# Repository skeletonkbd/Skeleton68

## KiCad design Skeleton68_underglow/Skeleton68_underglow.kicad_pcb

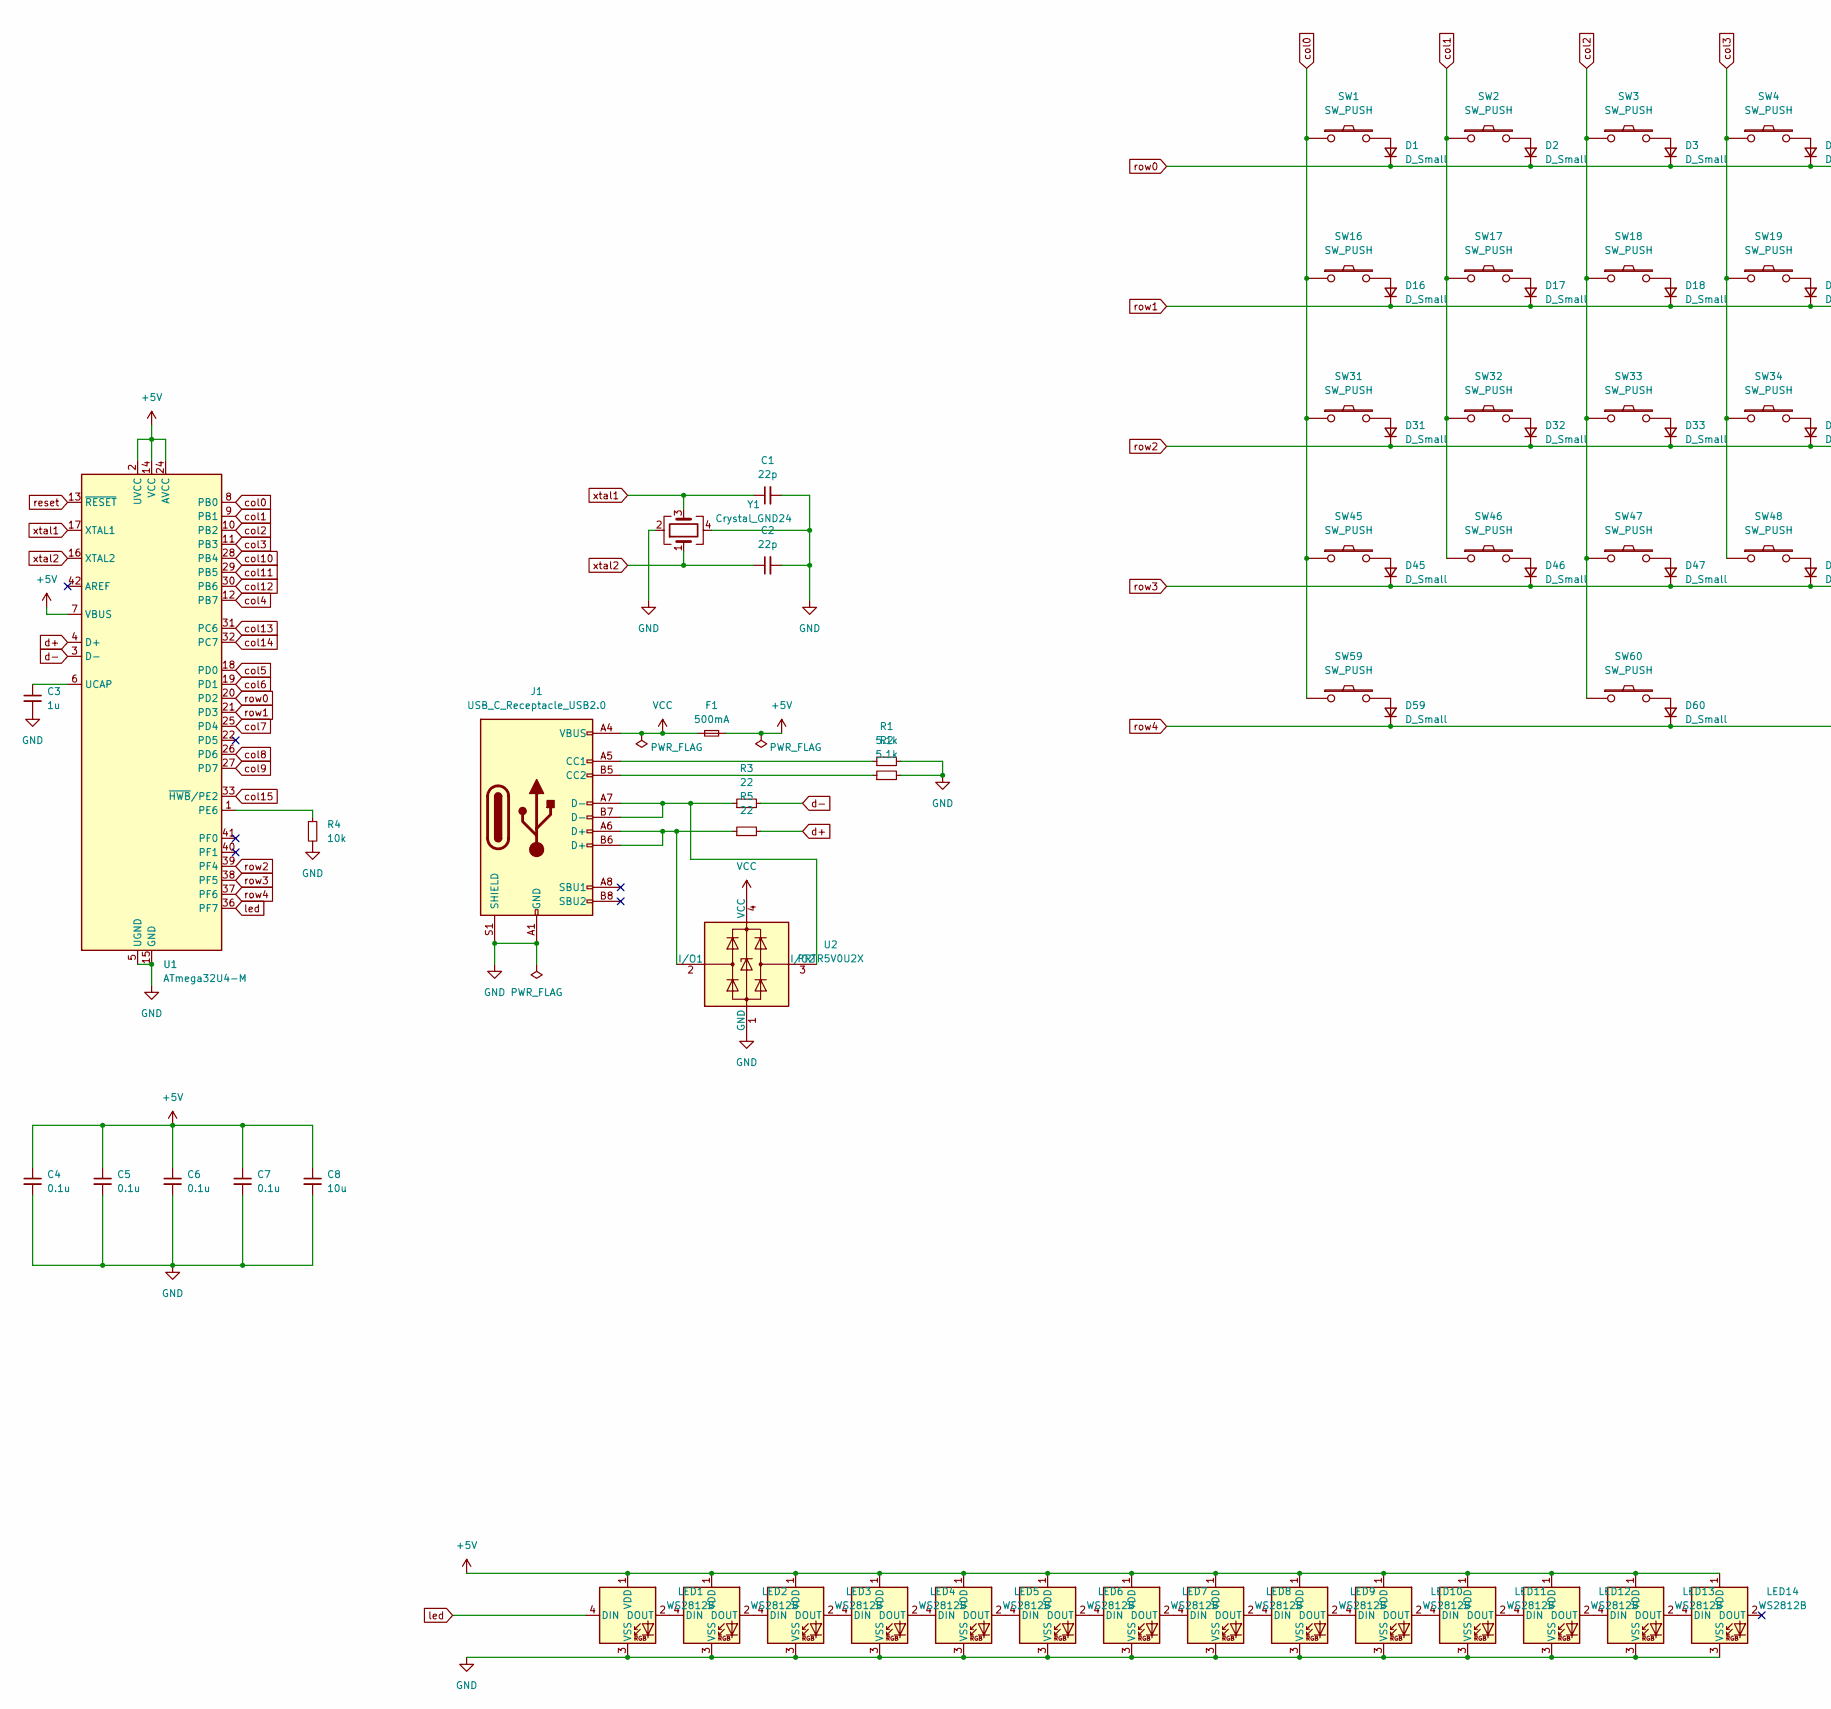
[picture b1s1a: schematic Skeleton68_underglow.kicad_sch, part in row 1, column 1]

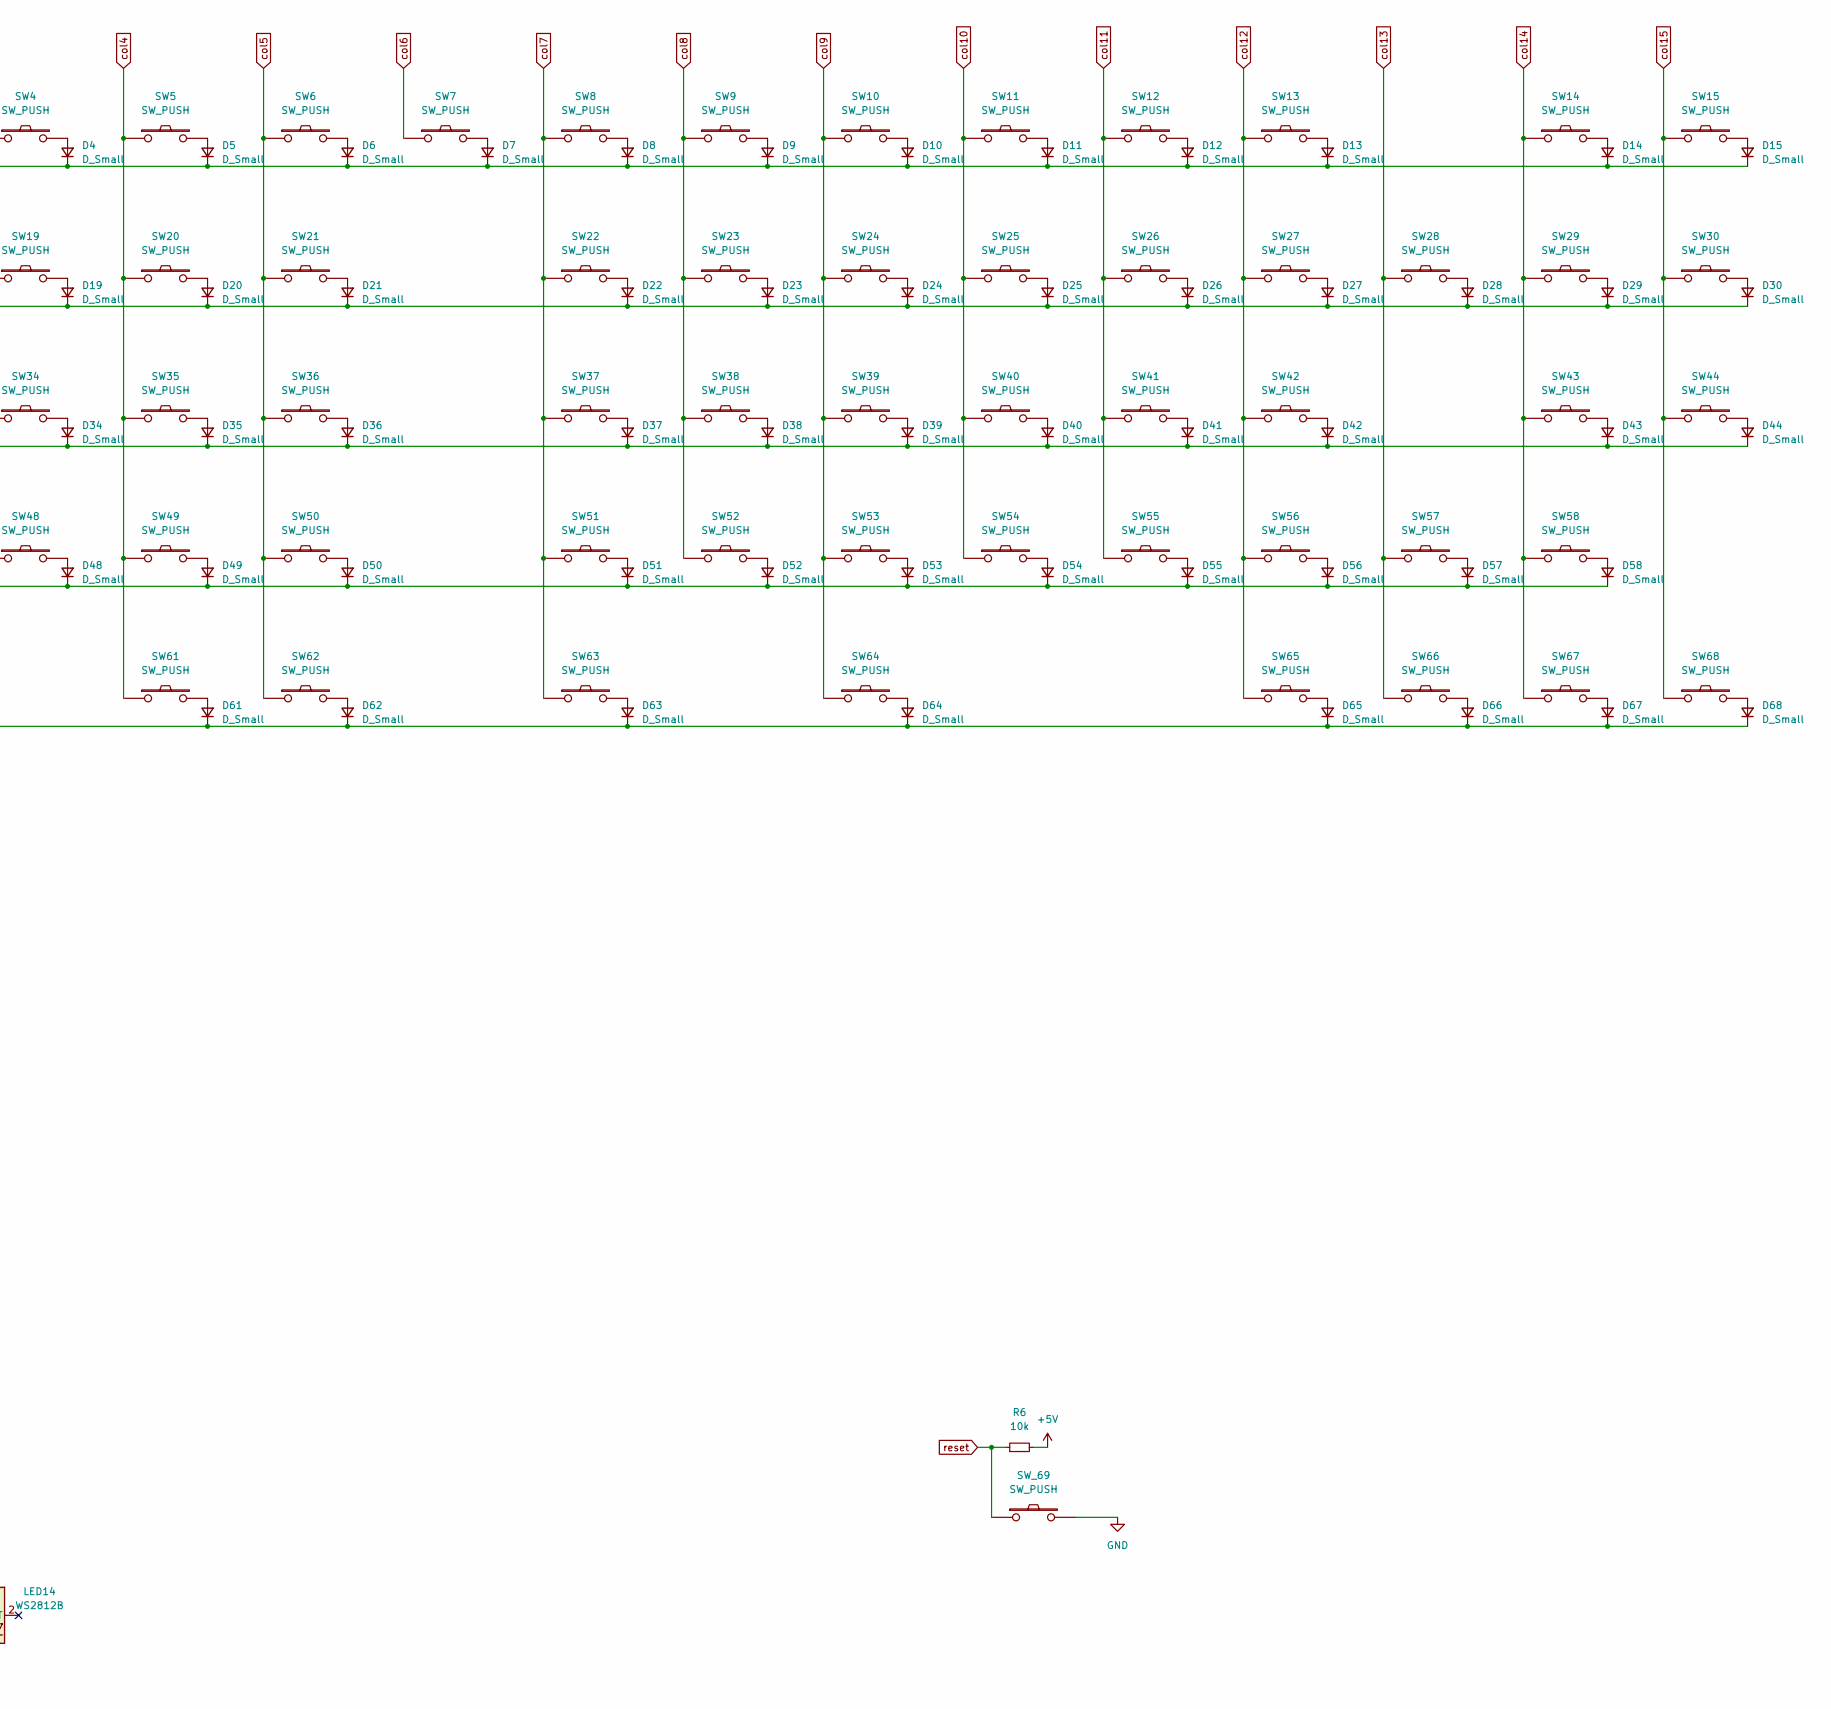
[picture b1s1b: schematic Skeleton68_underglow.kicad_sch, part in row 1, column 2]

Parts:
C1, C2: 22p; C_0805_2012Metric; LCSC C1804
C3: 1u; C_0805_2012Metric; LCSC C28323
C4, C5, C6, C7: 0.1u; C_0805_2012Metric; LCSC C49678
C8: 10u; C_0805_2012Metric; LCSC C15850
D1, D2, D3, D4, D5, D6, D7, D8, D9, D10, D11, D12, D13, D14, D15, D16, D17, D18, D19, D20, D21, D22, D23, D24, D25, D26, D27, D28, D29, D30, D31, D32, D33, D34, D35, D36, D37, D38, D39, D40, D41, D42, D43, D44, D45, D46, D47, D48, D49, D50, D51, D52, D53, D54, D55, D56, D57, D58, D59, D60, D61, D62, D63, D64, D65, D66, D67, D68: D_Small; D_SOD-123; LCSC C81598
F1: 500mA; Fuse_1206_3216Metric; LCSC C70069
J1: USB_C_Receptacle_USB2.0; USB_C_Receptacle_Palconn_UTC16-G; LCSC C167321
LED1, LED2, LED3, LED4, LED5, LED6, LED7, LED8, LED9, LED10, LED11, LED12, LED13, LED14: WS2812B; LED_WS2812B_PLCC4_5.0x5.0mm_P3.2mm; LCSC C2874885
R1, R2: 5.1k; R_0805_2012Metric; LCSC C27834
R3, R5: 22; R_0805_2012Metric; LCSC C17561
R4, R6: 10k; R_0805_2012Metric; LCSC C17414
SW1, SW2, SW3, SW4, SW5, SW6, SW7, SW8, SW9, SW10, SW11, SW12, SW13, SW15, SW17, SW18, SW19, SW20, SW21, SW22, SW23, SW24, SW25, SW26, SW27, SW28, SW30, SW32, SW33, SW34, SW35, SW36, SW37, SW38, SW39, SW40, SW41, SW42, SW44, SW46, SW47, SW48, SW49, SW50, SW51, SW52, SW53, SW54, SW55, SW56, SW58, SW62, SW66, SW67, SW68: SW_PUSH; MXOnly-1U-Hotswap; LCSC C2803348
SW14: SW_PUSH; MXOnly-2U-Hotswap; LCSC C2803348
SW16, SW29, SW59, SW60, SW64, SW65: SW_PUSH; MXOnly-1.5U-Hotswap; LCSC C2803348
SW31, SW57: SW_PUSH; MXOnly-1.75U-Hotswap; LCSC C2803348
SW43, SW45: SW_PUSH; MXOnly-2.25U-Hotswap; LCSC C2803348
SW61: SW_PUSH; MXOnly-2U-Hotswap-ReversedStabilizers; LCSC C2803348
SW63: SW_PUSH; MXOnly-2.75U-Hotswap-ReversedStabilizers; LCSC C2803348
SW_69: SW_PUSH; SW_SPST_SKQG_WithStem; LCSC C455263
U1: ATmega32U4-M; QFN-44-1EP_7x7mm_P0.5mm_EP5.2x5.2mm; LCSC C45874
U2: PRTR5V0U2X; SOT-143; LCSC C2827688
Y1: Crystal_GND24; Crystal_SMD_3225-4Pin_3.2x2.5mm; LCSC C13738

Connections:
+5V: C4.1, C5.1, C6.1, C7.1, C8.1, F1.2, LED1.1 (VDD), LED2.1 (VDD), LED3.1 (VDD), LED4.1 (VDD), LED5.1 (VDD), LED6.1 (VDD), LED7.1 (VDD), LED8.1 (VDD), LED9.1 (VDD), LED10.1 (VDD), LED11.1 (VDD), LED12.1 (VDD), LED13.1 (VDD), LED14.1 (VDD), R6.2, U1.2 (UVCC), U1.7 (VBUS), U1.14 (VCC), U1.24 (AVCC), U1.34 (VCC), U1.44 (AVCC)
GND: C1.2, C2.2, C3.2, C4.2, C5.2, C6.2, C7.2, C8.2, J1.A1 (GND), J1.A12 (GND), J1.B1 (GND), J1.B12 (GND), J1.S1 (SHIELD), LED1.3 (VSS), LED2.3 (VSS), LED3.3 (VSS), LED4.3 (VSS), LED5.3 (VSS), LED6.3 (VSS), LED7.3 (VSS), LED8.3 (VSS), LED9.3 (VSS), LED10.3 (VSS), LED11.3 (VSS), LED12.3 (VSS), LED13.3 (VSS), LED14.3 (VSS), R1.2, R2.2, R4.2, SW_69.2, U1.5 (UGND), U1.15 (GND), U1.23 (GND), U1.35 (GND), U1.43 (GND), U1.45 (GND), U2.1 (GND), Y1.2, Y1.4
unnamed: C3.1, U1.6 (UCAP)
unnamed: D1.2 (A), SW1.2
unnamed: D2.2 (A), SW2.2
unnamed: D3.2 (A), SW3.2
unnamed: D4.2 (A), SW4.2
unnamed: D5.2 (A), SW5.2
unnamed: D6.2 (A), SW6.2
unnamed: D7.2 (A), SW7.2
unnamed: D8.2 (A), SW8.2
unnamed: D9.2 (A), SW9.2
unnamed: D10.2 (A), SW10.2
unnamed: D11.2 (A), SW11.2
unnamed: D12.2 (A), SW12.2
unnamed: D13.2 (A), SW13.2
unnamed: D14.2 (A), SW14.2
unnamed: D15.2 (A), SW15.2
unnamed: D16.2 (A), SW16.2
unnamed: D17.2 (A), SW17.2
unnamed: D18.2 (A), SW18.2
unnamed: D19.2 (A), SW19.2
unnamed: D20.2 (A), SW20.2
unnamed: D21.2 (A), SW21.2
unnamed: D22.2 (A), SW22.2
unnamed: D23.2 (A), SW23.2
unnamed: D24.2 (A), SW24.2
unnamed: D25.2 (A), SW25.2
unnamed: D26.2 (A), SW26.2
unnamed: D27.2 (A), SW27.2
unnamed: D28.2 (A), SW28.2
unnamed: D29.2 (A), SW29.2
unnamed: D30.2 (A), SW30.2
unnamed: D31.2 (A), SW31.2
unnamed: D32.2 (A), SW32.2
unnamed: D33.2 (A), SW33.2
unnamed: D34.2 (A), SW34.2
unnamed: D35.2 (A), SW35.2
unnamed: D36.2 (A), SW36.2
unnamed: D37.2 (A), SW37.2
unnamed: D38.2 (A), SW38.2
unnamed: D39.2 (A), SW39.2
unnamed: D40.2 (A), SW40.2
unnamed: D41.2 (A), SW41.2
unnamed: D42.2 (A), SW42.2
unnamed: D43.2 (A), SW43.2
unnamed: D44.2 (A), SW44.2
unnamed: D45.2 (A), SW45.2
unnamed: D46.2 (A), SW46.2
unnamed: D47.2 (A), SW47.2
unnamed: D48.2 (A), SW48.2
unnamed: D49.2 (A), SW49.2
unnamed: D50.2 (A), SW50.2
unnamed: D51.2 (A), SW51.2
unnamed: D52.2 (A), SW52.2
unnamed: D53.2 (A), SW53.2
unnamed: D54.2 (A), SW54.2
unnamed: D55.2 (A), SW55.2
unnamed: D56.2 (A), SW56.2
unnamed: D57.2 (A), SW57.2
unnamed: D58.2 (A), SW58.2
unnamed: D59.2 (A), SW59.2
unnamed: D60.2 (A), SW60.2
unnamed: D61.2 (A), SW61.2
unnamed: D62.2 (A), SW62.2
unnamed: D63.2 (A), SW63.2
unnamed: D64.2 (A), SW64.2
unnamed: D65.2 (A), SW65.2
unnamed: D66.2 (A), SW66.2
unnamed: D67.2 (A), SW67.2
unnamed: D68.2 (A), SW68.2
unnamed: J1.A5 (CC1), R1.1
unnamed: J1.A6 (D+), J1.B6 (D+), R5.1, U2.2 (I/O1)
unnamed: J1.A7 (D-), J1.B7 (D-), R3.1, U2.3 (I/O2)
unnamed: J1.B5 (CC2), R2.1
unnamed: LED1.2 (DOUT), LED2.4 (DIN)
unnamed: LED2.2 (DOUT), LED3.4 (DIN)
unnamed: LED3.2 (DOUT), LED4.4 (DIN)
unnamed: LED4.2 (DOUT), LED5.4 (DIN)
unnamed: LED5.2 (DOUT), LED6.4 (DIN)
unnamed: LED6.2 (DOUT), LED7.4 (DIN)
unnamed: LED7.2 (DOUT), LED8.4 (DIN)
unnamed: LED8.2 (DOUT), LED9.4 (DIN)
unnamed: LED10.2 (DOUT), LED11.4 (DIN)
unnamed: LED9.2 (DOUT), LED10.4 (DIN)
unnamed: LED11.2 (DOUT), LED12.4 (DIN)
unnamed: LED12.2 (DOUT), LED13.4 (DIN)
unnamed: LED13.2 (DOUT), LED14.4 (DIN)
unnamed: R4.1, U1.1 (PE6)
VCC: F1.1, J1.A4 (VBUS), J1.A9 (VBUS), J1.B4 (VBUS), J1.B9 (VBUS), U2.4 (VCC)
col0: SW1.1, SW16.1, SW31.1, SW45.1, SW59.1, U1.8 (PB0)
col1: SW2.1, SW17.1, SW32.1, SW46.1, U1.9 (PB1)
col2: SW3.1, SW18.1, SW33.1, SW47.1, SW60.1, U1.10 (PB2)
col3: SW4.1, SW19.1, SW34.1, SW48.1, U1.11 (PB3)
col4: SW5.1, SW20.1, SW35.1, SW49.1, SW61.1, U1.12 (PB7)
col5: SW6.1, SW21.1, SW36.1, SW50.1, SW62.1, U1.18 (PD0)
col6: SW7.1, U1.19 (PD1)
col7: SW8.1, SW22.1, SW37.1, SW51.1, SW63.1, U1.25 (PD4)
col8: SW9.1, SW23.1, SW38.1, SW52.1, U1.26 (PD6)
col9: SW10.1, SW24.1, SW39.1, SW53.1, SW64.1, U1.27 (PD7)
col10: SW11.1, SW25.1, SW40.1, SW54.1, U1.28 (PB4)
col11: SW12.1, SW26.1, SW41.1, SW55.1, U1.29 (PB5)
col12: SW13.1, SW27.1, SW42.1, SW56.1, SW65.1, U1.30 (PB6)
col13: SW28.1, SW57.1, SW66.1, U1.31 (PC6)
col14: SW14.1, SW29.1, SW43.1, SW58.1, SW67.1, U1.32 (PC7)
col15: SW15.1, SW30.1, SW44.1, SW68.1, U1.33 (~HWB/PE2)
d+: R5.2, U1.4 (D+)
d-: R3.2, U1.3 (D-)
led: LED1.4 (DIN), U1.36 (PF7)
reset: R6.1, SW_69.1, U1.13 (~RESET)
row0: D1.1 (K), D2.1 (K), D3.1 (K), D4.1 (K), D5.1 (K), D6.1 (K), D7.1 (K), D8.1 (K), D9.1 (K), D10.1 (K), D11.1 (K), D12.1 (K), D13.1 (K), D14.1 (K), D15.1 (K), U1.20 (PD2)
row1: D16.1 (K), D17.1 (K), D18.1 (K), D19.1 (K), D20.1 (K), D21.1 (K), D22.1 (K), D23.1 (K), D24.1 (K), D25.1 (K), D26.1 (K), D27.1 (K), D28.1 (K), D29.1 (K), D30.1 (K), U1.21 (PD3)
row2: D31.1 (K), D32.1 (K), D33.1 (K), D34.1 (K), D35.1 (K), D36.1 (K), D37.1 (K), D38.1 (K), D39.1 (K), D40.1 (K), D41.1 (K), D42.1 (K), D43.1 (K), D44.1 (K), U1.39 (PF4)
row3: D45.1 (K), D46.1 (K), D47.1 (K), D48.1 (K), D49.1 (K), D50.1 (K), D51.1 (K), D52.1 (K), D53.1 (K), D54.1 (K), D55.1 (K), D56.1 (K), D57.1 (K), D58.1 (K), U1.38 (PF5)
row4: D59.1 (K), D60.1 (K), D61.1 (K), D62.1 (K), D63.1 (K), D64.1 (K), D65.1 (K), D66.1 (K), D67.1 (K), D68.1 (K), U1.37 (PF6)
xtal1: C1.1, U1.17 (XTAL1), Y1.3
xtal2: C2.1, U1.16 (XTAL2), Y1.1

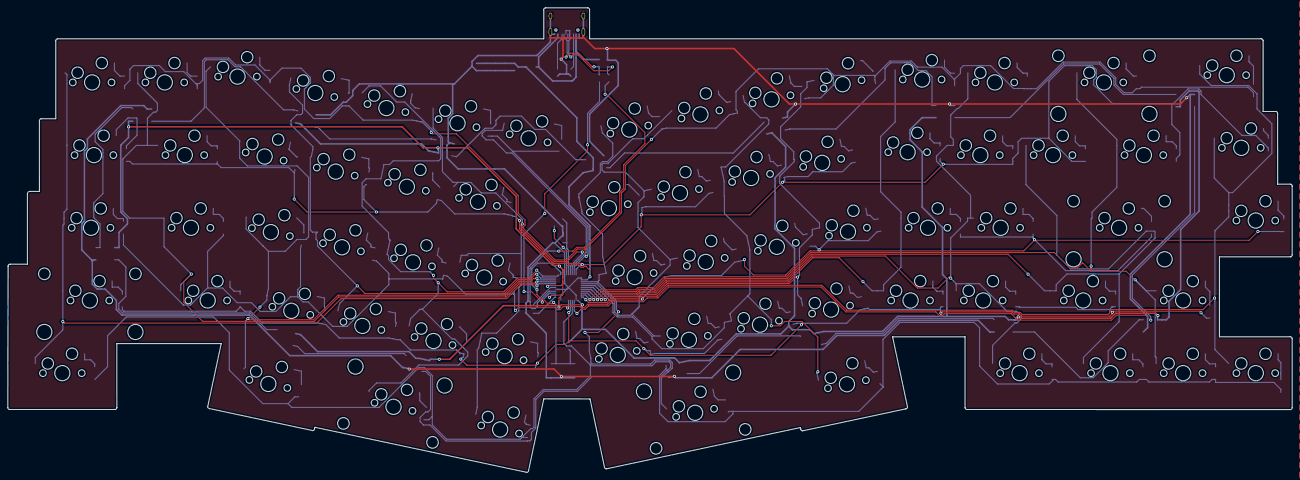
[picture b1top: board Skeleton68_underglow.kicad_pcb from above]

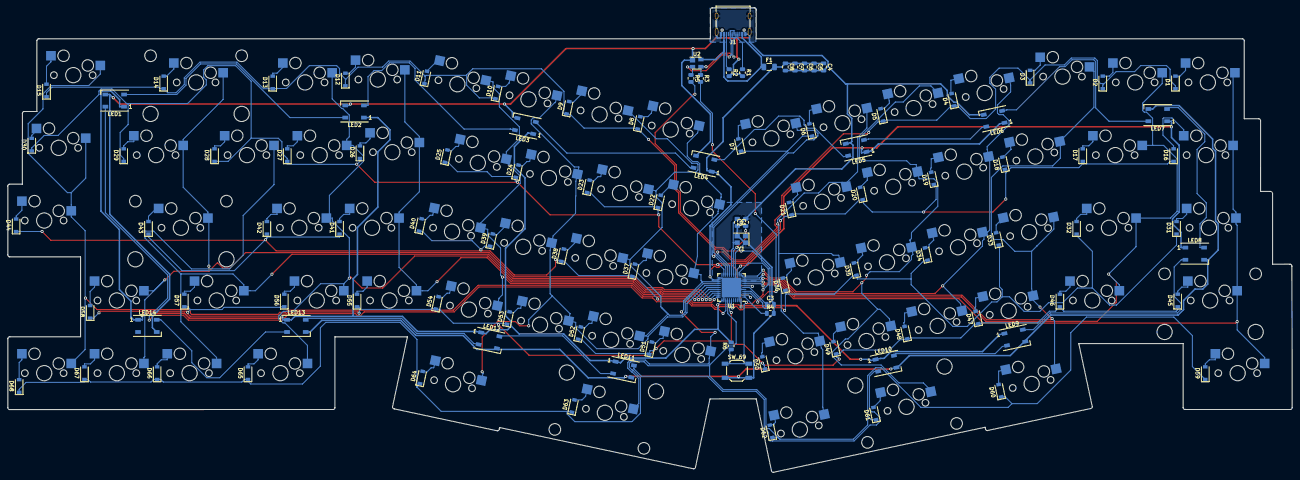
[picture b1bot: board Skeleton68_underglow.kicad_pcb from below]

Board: 2 copper layers, 336.6 x 121.7 mm, 170 parts (170 on the bottom side), 117 nets.

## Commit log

2022-06-07 trial
2022-06-07 prototype
2022-06-07 added library
2022-07-28 release
2022-07-29 routed
2022-07-29 routed2
2022-09-17 add underglow version
2023-09-14 add firmware
